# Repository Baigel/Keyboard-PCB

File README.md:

# Keyboard-PCB
A collection of PCB keyboards that run QMK - all in various states of completion

### Changes to Make
To PCBs
 - Oscillator to C122519
- Oscillator Load Caps to 20pF (including lcsc)
- Fix LEDs LCSC code to be correct (make sure it is C5149201)
- CC pins on USB C should be 5.1k
- Add lcsc C5156480 to sockets
- USB C to C2927038
- Change all diodes to C5345962
- Make sure Ctrl then Win then Alt
- Change Fn to Win

To Firmware:
 - Add separate firmware for different boards where relevatn
 - Add MacOS firmware versions

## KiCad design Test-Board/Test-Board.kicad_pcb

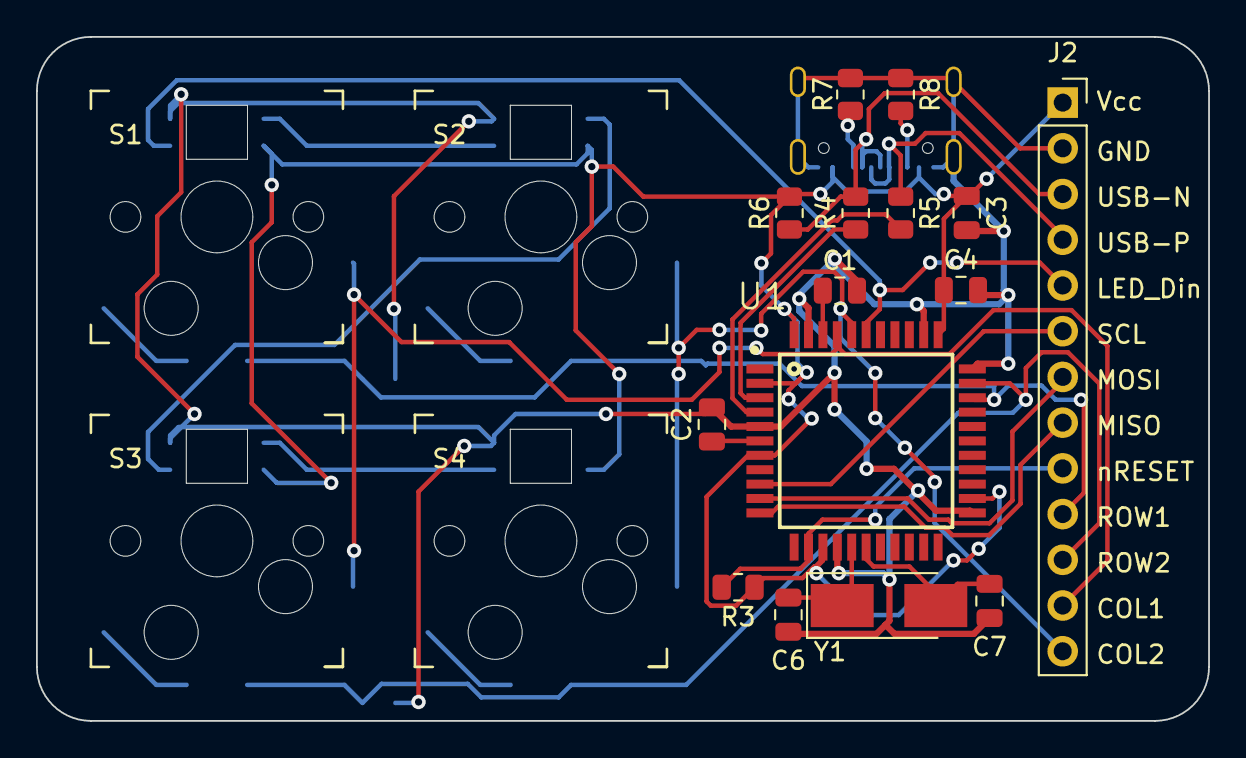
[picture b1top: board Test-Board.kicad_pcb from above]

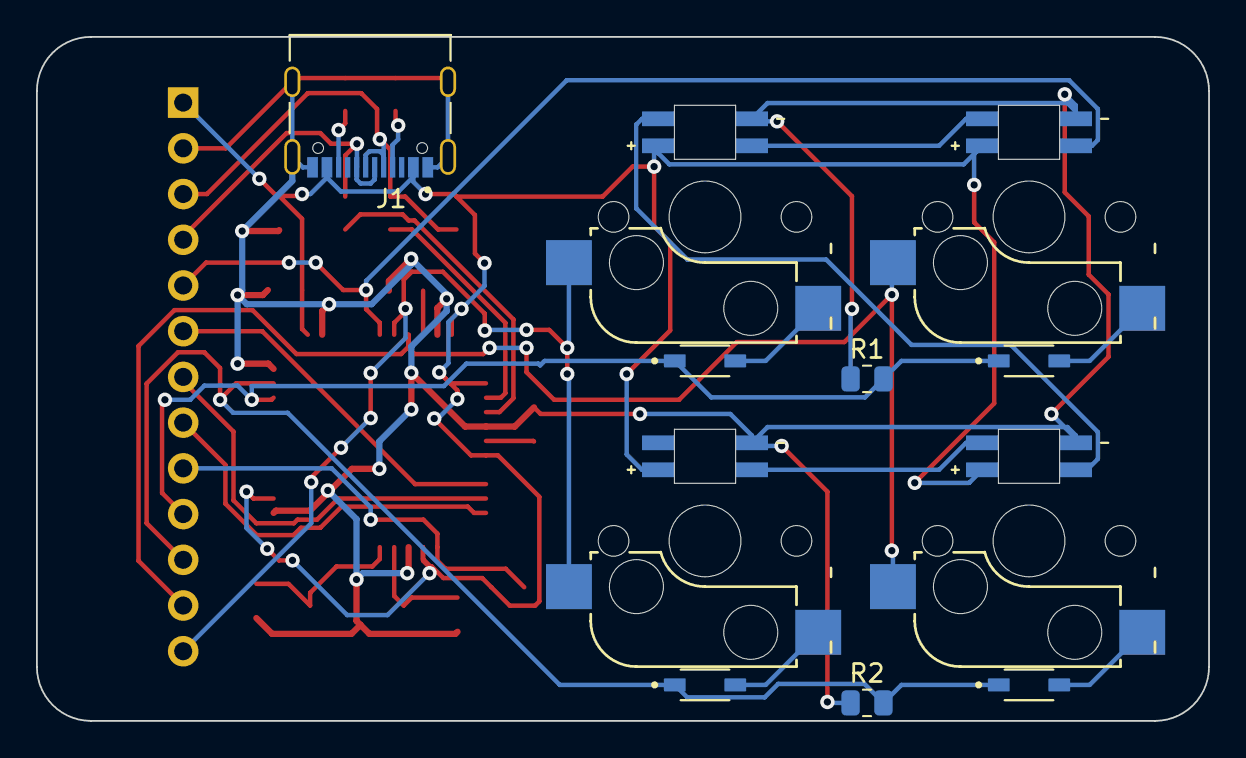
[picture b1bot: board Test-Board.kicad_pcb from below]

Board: 2 copper layers, 65.1 x 38.0 mm, 30 parts (11 on the bottom side), 28 nets.

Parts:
C1, C3: 0.1uF; C_0805_2012Metric
C2, C4: 1uF; C_0805_2012Metric
C6, C7: 20pF; C_0805_2012Metric
D1, D2, D3, D4: 1N4148; SOD3715X135N
J1: TYPE-C-31-M-12; HRO_TYPE-C-31-M-12
J2: Conn_01x13_Pin; PinSocket_1x13_P2.54mm_Vertical
L1, L2, L3, L4: SK6812-E; LED_SK6812-E
R1, R2, R3, R7, R8: 10k; R_0805_2012Metric
R4, R5: 22R; R_0805_2012Metric
R6: 15k; R_0805_2012Metric
SW1: S1; Kailh_socket_MX
SW2: S2; Kailh_socket_MX
SW3: S3; Kailh_socket_MX
SW4: S4; Kailh_socket_MX
U1: ATMEGA32U4-AU; QFP80P1200X1200X120-44N
Y1: 16MHz; Crystal_SMD_5032-2Pin_5.0x3.2mm_HandSoldering

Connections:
AREF: C1.1, U1.42 (AREF)
COL1: J2.12, SW1.2, SW3.2, U1.41 (PF0)
COL2: J2.13, SW2.2, SW4.2, U1.40 (PF1)
GND: C1.2, C2.2, C3.2, C4.2, C6.1, C7.2, J1.A1_B12 (GND), J1.B1_A12 (GND), J1.S1 (SHIELD), J1.S2 (SHIELD), J1.S3 (SHIELD), J1.S4 (SHIELD), J2.2, L1.3 (GND), L2.3 (GND), L3.3 (GND), L4.3 (GND), R1.1, R2.1, R7.1, R8.1, U1.5 (UGND), U1.15 (GND), U1.23 (GND), U1.33 (PE2), U1.35 (GND), U1.43 (GND)
LED_DIN: J2.5, L1.4 (DIN), U1.39 (PF4)
MISO: J2.8, U1.11 (PB3)
MOSI: J2.7, U1.10 (PB2)
unnamed: D1.A, SW1.1
unnamed: D2.A, SW2.1
unnamed: D3.A, SW3.1
unnamed: D4.A, SW4.1
unnamed: J1.A5 (CC1), R7.2
unnamed: J1.B5 (CC2), R8.2
unnamed: L1.2 (DOUT), L2.4 (DIN)
unnamed: L2.2 (DOUT), L3.4 (DIN)
unnamed: L3.2 (DOUT), L4.4 (DIN)
unnamed: R5.1, U1.4 (D+)
unnamed: R4.1, U1.3 (D-)
ROW1: D1.C, D2.C, J2.10, R1.2, U1.31 (PC6)
ROW2: D3.C, D4.C, J2.11, R2.2, U1.32 (PC7)
SCL: J2.6, U1.9 (PB1)
UCAP: C2.1, U1.6 (UCAP)
USB-N: J1.A7 (DN1), J1.B7 (DN2), J2.3, R4.2, R6.1
USB-P: J1.A6 (DP1), J1.B6 (DP2), J2.4, R5.2
VCC: C3.1, C4.1, J1.A4_B9 (VBUS), J1.B4_A9 (VBUS), J2.1, L1.1 (VDD), L2.1 (VDD), L3.1 (VDD), L4.1 (VDD), R3.1, R6.2, U1.2 (UVCC), U1.7 (VBUS), U1.14 (VCC), U1.24 (AVCC), U1.34 (VCC), U1.44 (AVCC)
XTAL1: C7.1, U1.17 (XTAL1), Y1.2
XTAL2: C6.2, U1.16 (XTAL2), Y1.1
nRESET: J2.9, R3.2, U1.13 (~RESET)

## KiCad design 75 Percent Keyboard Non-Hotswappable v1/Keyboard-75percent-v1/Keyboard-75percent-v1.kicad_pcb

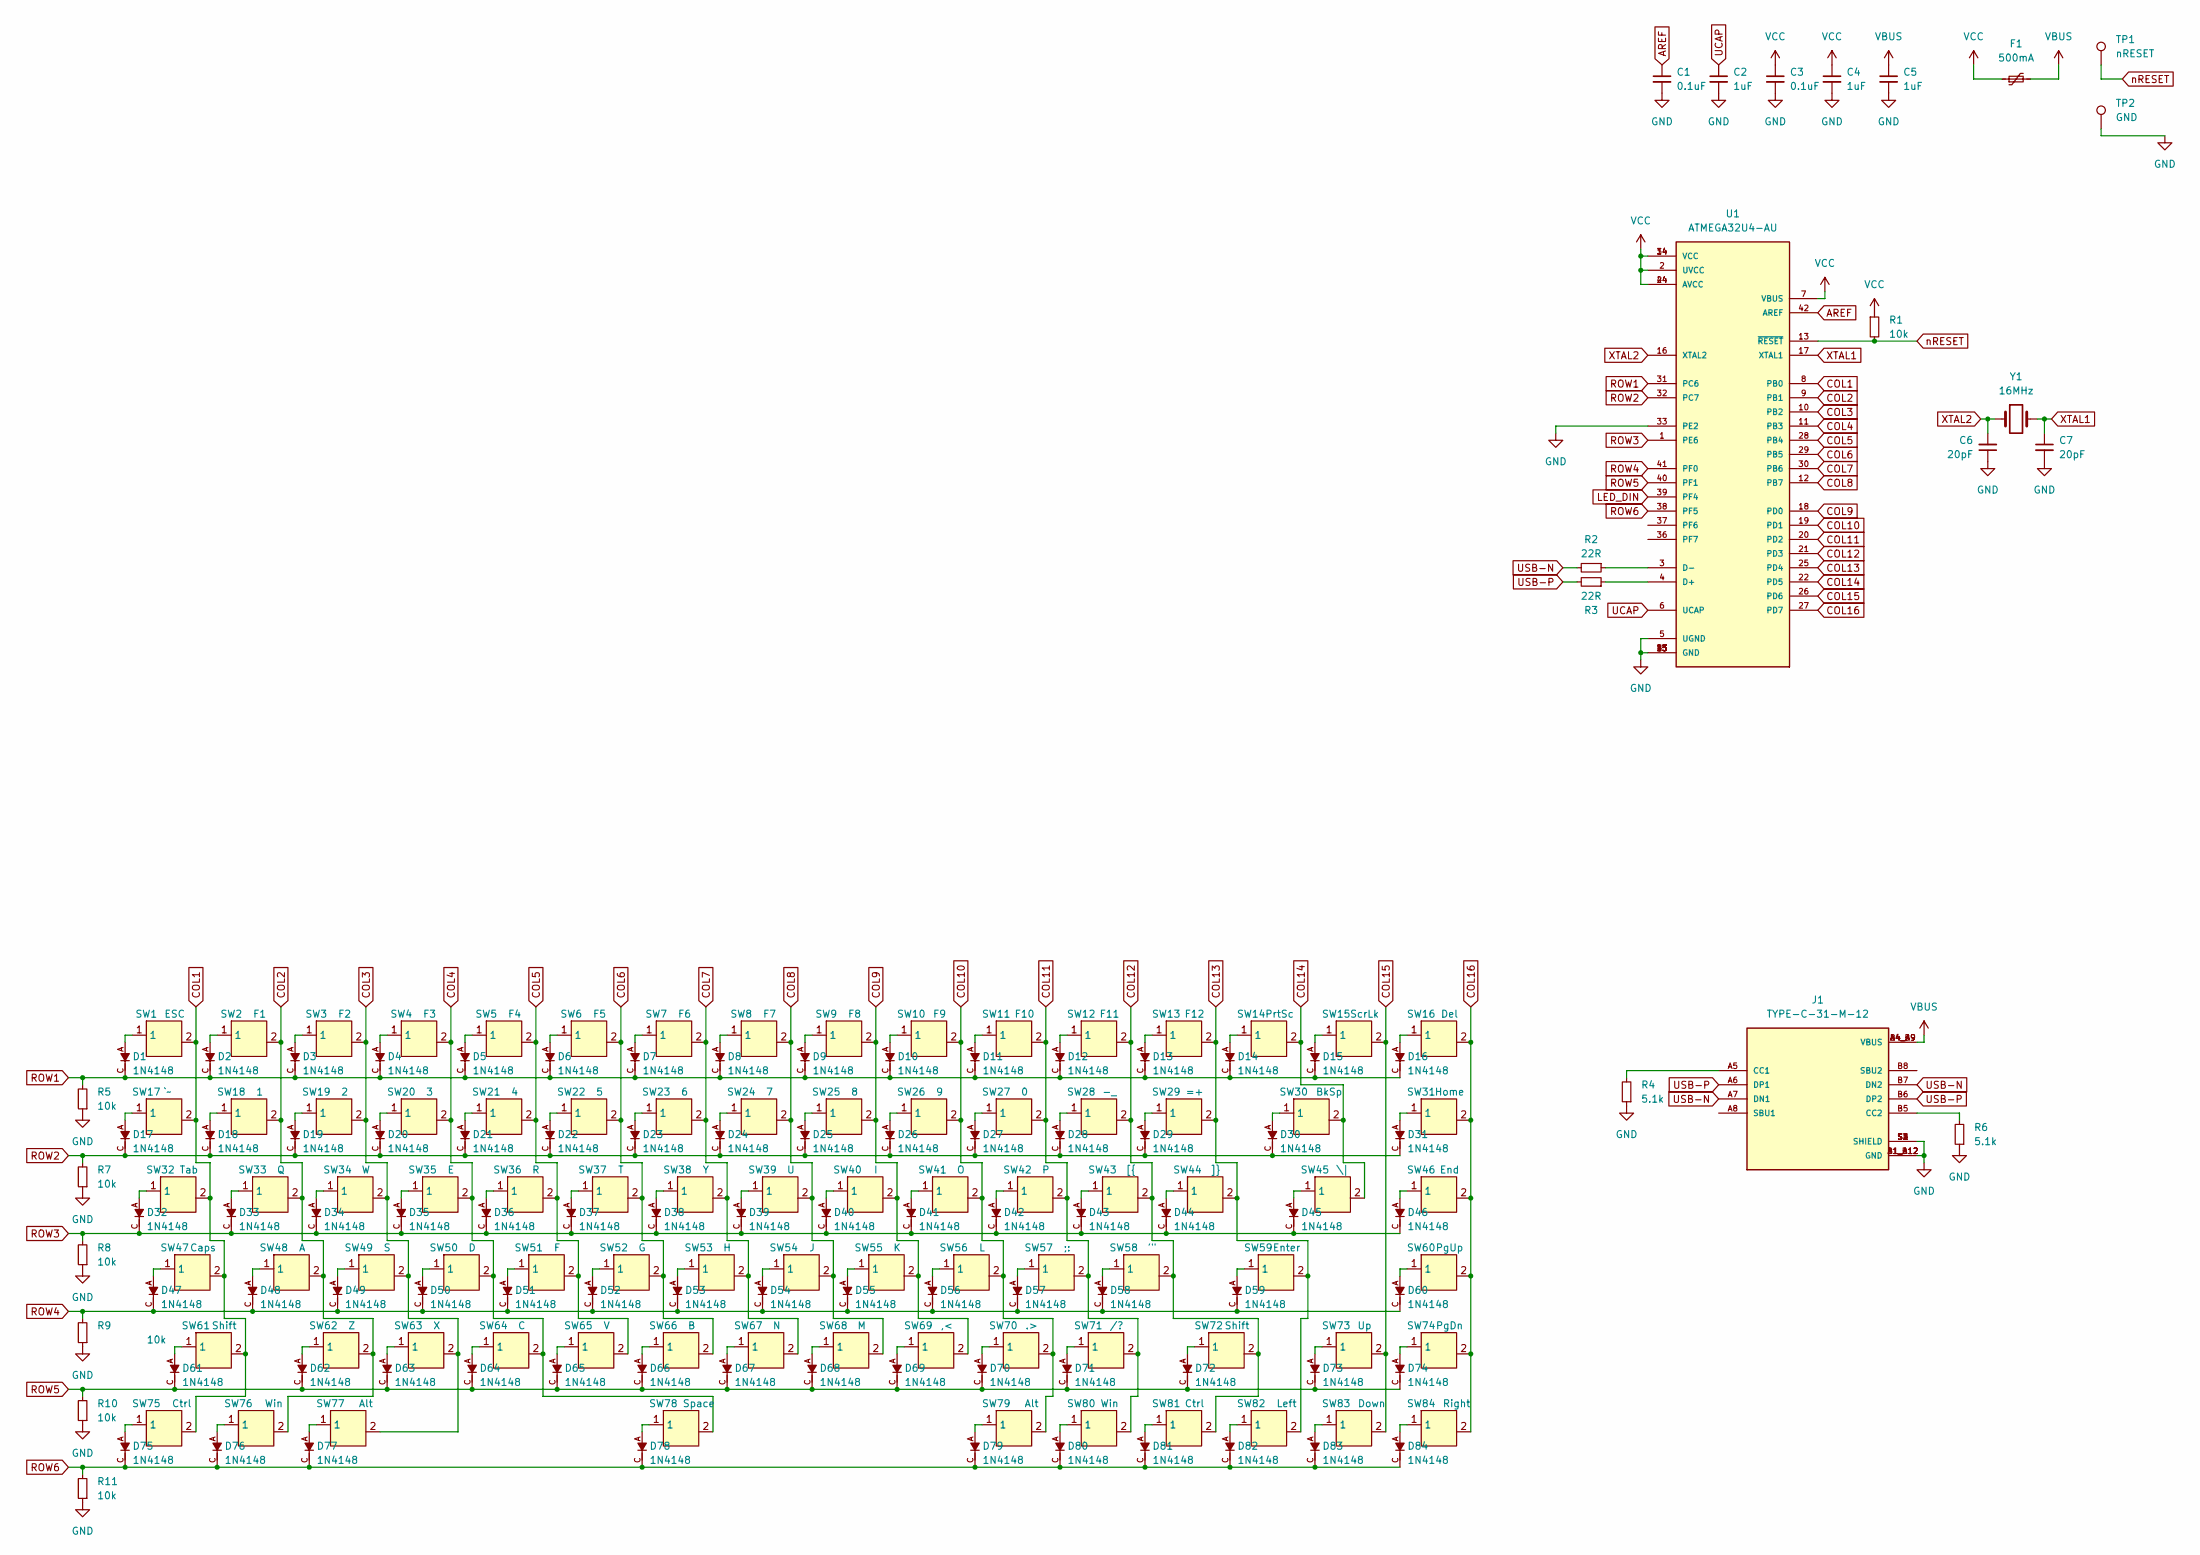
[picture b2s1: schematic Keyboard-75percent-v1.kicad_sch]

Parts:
C1, C3: 0.1uF; C_0805_2012Metric; LCSC C476766
C2, C4, C5: 1uF; C_0805_2012Metric; LCSC C152857
C6, C7: 20pF; C_0805_2012Metric; LCSC C2209222
D1, D2, D3, D4, D5, D6, D7, D8, D9, D10, D11, D12, D13, D14, D15, D16, D17, D18, D19, D20, D21, D22, D23, D24, D25, D26, D27, D28, D29, D30, D31, D32, D33, D34, D35, D36, D37, D38, D39, D40, D41, D42, D43, D44, D45, D46, D47, D48, D49, D50, D51, D52, D53, D54, D55, D56, D57, D58, D59, D60, D61, D62, D63, D64, D65, D66, D67, D68, D69, D70, D71, D72, D73, D74, D75, D76, D77, D78, D79, D80, D81, D82, D83, D84: 1N4148; SOD3715X135N; PARTREV 28-2; LCSC C5345962
F1: 500mA; R_0805_2012Metric_Pad1.20x1.40mm_HandSolder; LCSC C2649565
J1: TYPE-C-31-M-12; HRO_TYPE-C-31-M-12; PARTREV 2020.12.08; LCSC C2927038
R1, R5, R7, R8, R9, R10, R11: 10k; R_0805_2012Metric; LCSC C2075621
R2, R3: 22R; R_0805_2012Metric; LCSC C4349165
R4, R6: 5.1k; R_0805_2012Metric; LCSC C2079038
SW1: ESC; SW_Cherry_MX_1.00u_PCB
SW2: F1; SW_Cherry_MX_1.00u_PCB
SW3: F2; SW_Cherry_MX_1.00u_PCB
SW4: F3; SW_Cherry_MX_1.00u_PCB
SW5: F4; SW_Cherry_MX_1.00u_PCB
SW6: F5; SW_Cherry_MX_1.00u_PCB
SW7: F6; SW_Cherry_MX_1.00u_PCB
SW8: F7; SW_Cherry_MX_1.00u_PCB
SW9: F8; SW_Cherry_MX_1.00u_PCB
SW10: F9; SW_Cherry_MX_1.00u_PCB
SW11: F10; SW_Cherry_MX_1.00u_PCB
SW12: F11; SW_Cherry_MX_1.00u_PCB
SW13: F12; SW_Cherry_MX_1.00u_PCB
SW14: PrtSc; SW_Cherry_MX_1.00u_PCB
SW15: ScrLk; SW_Cherry_MX_1.00u_PCB
SW16: Del; SW_Cherry_MX_1.00u_PCB
SW17: `~; SW_Cherry_MX_1.00u_PCB
SW18: 1; SW_Cherry_MX_1.00u_PCB
SW19: 2; SW_Cherry_MX_1.00u_PCB
SW20: 3; SW_Cherry_MX_1.00u_PCB
SW21: 4; SW_Cherry_MX_1.00u_PCB
SW22: 5; SW_Cherry_MX_1.00u_PCB
SW23: 6; SW_Cherry_MX_1.00u_PCB
SW24: 7; SW_Cherry_MX_1.00u_PCB
SW25: 8; SW_Cherry_MX_1.00u_PCB
SW26: 9; SW_Cherry_MX_1.00u_PCB
SW27: 0; SW_Cherry_MX_1.00u_PCB
SW28: -_; SW_Cherry_MX_1.00u_PCB
SW29: =+; SW_Cherry_MX_1.00u_PCB
SW30: BkSp; SW_Cherry_MX_2.00u_PCB
SW31: Home; SW_Cherry_MX_1.00u_PCB
SW32: Tab; SW_Cherry_MX_1.50u_PCB
SW33: Q; SW_Cherry_MX_1.00u_PCB
SW34: W; SW_Cherry_MX_1.00u_PCB
SW35: E; SW_Cherry_MX_1.00u_PCB
SW36: R; SW_Cherry_MX_1.00u_PCB
SW37: T; SW_Cherry_MX_1.00u_PCB
SW38: Y; SW_Cherry_MX_1.00u_PCB
SW39: U; SW_Cherry_MX_1.00u_PCB
SW40: I; SW_Cherry_MX_1.00u_PCB
SW41: O; SW_Cherry_MX_1.00u_PCB
SW42: P; SW_Cherry_MX_1.00u_PCB
SW43: [{; SW_Cherry_MX_1.00u_PCB
SW44: ]}; SW_Cherry_MX_1.00u_PCB
SW45: \|; SW_Cherry_MX_1.50u_PCB
SW46: End; SW_Cherry_MX_1.00u_PCB
SW47: Caps; SW_Cherry_MX_1.75u_PCB
SW48: A; SW_Cherry_MX_1.00u_PCB
SW49: S; SW_Cherry_MX_1.00u_PCB
SW50: D; SW_Cherry_MX_1.00u_PCB
SW51: F; SW_Cherry_MX_1.00u_PCB
SW52: G; SW_Cherry_MX_1.00u_PCB
SW53: H; SW_Cherry_MX_1.00u_PCB
SW54: J; SW_Cherry_MX_1.00u_PCB
SW55: K; SW_Cherry_MX_1.00u_PCB
SW56: L; SW_Cherry_MX_1.00u_PCB
SW57: ;:; SW_Cherry_MX_1.00u_PCB
SW58: '"; SW_Cherry_MX_1.00u_PCB
SW59: Enter; SW_Cherry_MX_2.25u_PCB
SW60: PgUp; SW_Cherry_MX_1.00u_PCB
SW61: Shift; SW_Cherry_MX_2.25u_PCB
SW62: Z; SW_Cherry_MX_1.00u_PCB
SW63: X; SW_Cherry_MX_1.00u_PCB
SW64: C; SW_Cherry_MX_1.00u_PCB
SW65: V; SW_Cherry_MX_1.00u_PCB
SW66: B; SW_Cherry_MX_1.00u_PCB
SW67: N; SW_Cherry_MX_1.00u_PCB
SW68: M; SW_Cherry_MX_1.00u_PCB
SW69: ,<; SW_Cherry_MX_1.00u_PCB
SW70: .>; SW_Cherry_MX_1.00u_PCB
SW71: /?; SW_Cherry_MX_1.00u_PCB
SW72: Shift; SW_Cherry_MX_1.75u_PCB
SW73: Up; SW_Cherry_MX_1.00u_PCB
SW74: PgDn; SW_Cherry_MX_1.00u_PCB
SW75: Ctrl; SW_Cherry_MX_1.25u_PCB
SW76: Win; SW_Cherry_MX_1.25u_PCB
SW77: Alt; SW_Cherry_MX_1.25u_PCB
SW78: Space; SW_Cherry_MX_6.25u_PCB
SW79: Alt; SW_Cherry_MX_1.00u_PCB
SW80: Win; SW_Cherry_MX_1.00u_PCB
SW81: Ctrl; SW_Cherry_MX_1.00u_PCB
SW82: Left; SW_Cherry_MX_1.00u_PCB
SW83: Down; SW_Cherry_MX_1.00u_PCB
SW84: Right; SW_Cherry_MX_1.00u_PCB
TP1: nRESET; TestPoint_Pad_D2.0mm
TP2: GND; TestPoint_Pad_D2.0mm
U1: ATMEGA32U4-AU; QFP80P1200X1200X120-44N
Y1: 16MHz; Crystal_SMD_5032-2Pin_5.0x3.2mm_HandSoldering; LCSC C122519

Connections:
AREF: C1.1, U1.42 (AREF)
COL1: SW1.2, SW17.2, SW32.2, SW47.2, SW61.2, SW75.2, U1.8 (PB0)
COL2: SW2.2, SW18.2, SW33.2, SW48.2, SW62.2, SW76.2, U1.9 (PB1)
COL3: SW3.2, SW19.2, SW34.2, SW49.2, SW63.2, SW77.2, U1.10 (PB2)
COL4: SW4.2, SW20.2, SW35.2, SW50.2, SW64.2, SW78.2, U1.11 (PB3)
COL5: SW5.2, SW21.2, SW36.2, SW51.2, SW65.2, U1.28 (PB4)
COL6: SW6.2, SW22.2, SW37.2, SW52.2, SW66.2, U1.29 (PB5)
COL7: SW7.2, SW23.2, SW38.2, SW53.2, SW67.2, U1.30 (PB6)
COL8: SW8.2, SW24.2, SW39.2, SW54.2, SW68.2, U1.12 (PB7)
COL9: SW9.2, SW25.2, SW40.2, SW55.2, SW69.2, U1.18 (PD0)
COL10: SW10.2, SW26.2, SW41.2, SW56.2, SW70.2, SW79.2, U1.19 (PD1)
COL11: SW11.2, SW27.2, SW42.2, SW57.2, SW71.2, SW80.2, U1.20 (PD2)
COL12: SW12.2, SW28.2, SW43.2, SW58.2, SW72.2, SW81.2, U1.21 (PD3)
COL13: SW13.2, SW29.2, SW44.2, SW59.2, SW82.2, U1.25 (PD4)
COL14: SW14.2, SW30.2, SW45.2, U1.22 (PD5)
COL15: SW15.2, SW73.2, SW83.2, U1.26 (PD6)
COL16: SW16.2, SW31.2, SW46.2, SW60.2, SW74.2, SW84.2, U1.27 (PD7)
GND: C1.2, C2.2, C3.2, C4.2, C5.2, C6.1, C7.2, J1.A1_B12 (GND), J1.B1_A12 (GND), J1.S1 (SHIELD), J1.S2 (SHIELD), J1.S3 (SHIELD), J1.S4 (SHIELD), R4.1, R5.1, R6.1, R7.1, R8.1, R9.1, R10.1, R11.1, TP2.1, U1.5 (UGND), U1.15 (GND), U1.23 (GND), U1.33 (PE2), U1.35 (GND), U1.43 (GND)
LED_DIN: U1.39 (PF4)
unnamed: D1.A, SW1.1
unnamed: D2.A, SW2.1
unnamed: D3.A, SW3.1
unnamed: D4.A, SW4.1
unnamed: D5.A, SW5.1
unnamed: D6.A, SW6.1
unnamed: D7.A, SW7.1
unnamed: D8.A, SW8.1
unnamed: D9.A, SW9.1
unnamed: D10.A, SW10.1
unnamed: D11.A, SW11.1
unnamed: D12.A, SW12.1
unnamed: D13.A, SW13.1
unnamed: D14.A, SW14.1
unnamed: D15.A, SW15.1
unnamed: D16.A, SW16.1
unnamed: D17.A, SW17.1
unnamed: D18.A, SW18.1
unnamed: D19.A, SW19.1
unnamed: D20.A, SW20.1
unnamed: D21.A, SW21.1
unnamed: D22.A, SW22.1
unnamed: D23.A, SW23.1
unnamed: D24.A, SW24.1
unnamed: D25.A, SW25.1
unnamed: D26.A, SW26.1
unnamed: D27.A, SW27.1
unnamed: D28.A, SW28.1
unnamed: D29.A, SW29.1
unnamed: D30.A, SW30.1
unnamed: D31.A, SW31.1
unnamed: D32.A, SW32.1
unnamed: D33.A, SW33.1
unnamed: D34.A, SW34.1
unnamed: D35.A, SW35.1
unnamed: D36.A, SW36.1
unnamed: D37.A, SW37.1
unnamed: D38.A, SW38.1
unnamed: D39.A, SW39.1
unnamed: D40.A, SW40.1
unnamed: D41.A, SW41.1
unnamed: D42.A, SW42.1
unnamed: D43.A, SW43.1
unnamed: D44.A, SW44.1
unnamed: D45.A, SW45.1
unnamed: D46.A, SW46.1
unnamed: D47.A, SW47.1
unnamed: D48.A, SW48.1
unnamed: D49.A, SW49.1
unnamed: D50.A, SW50.1
unnamed: D51.A, SW51.1
unnamed: D52.A, SW52.1
unnamed: D53.A, SW53.1
unnamed: D54.A, SW54.1
unnamed: D55.A, SW55.1
unnamed: D56.A, SW56.1
unnamed: D57.A, SW57.1
unnamed: D58.A, SW58.1
unnamed: D59.A, SW59.1
unnamed: D60.A, SW60.1
unnamed: D61.A, SW61.1
unnamed: D62.A, SW62.1
unnamed: D63.A, SW63.1
unnamed: D64.A, SW64.1
unnamed: D65.A, SW65.1
unnamed: D66.A, SW66.1
unnamed: D67.A, SW67.1
unnamed: D68.A, SW68.1
unnamed: D69.A, SW69.1
unnamed: D70.A, SW70.1
unnamed: D71.A, SW71.1
unnamed: D72.A, SW72.1
unnamed: D73.A, SW73.1
unnamed: D74.A, SW74.1
unnamed: D75.A, SW75.1
unnamed: D76.A, SW76.1
unnamed: D77.A, SW77.1
unnamed: D78.A, SW78.1
unnamed: D79.A, SW79.1
unnamed: D80.A, SW80.1
unnamed: D81.A, SW81.1
unnamed: D82.A, SW82.1
unnamed: D83.A, SW83.1
unnamed: D84.A, SW84.1
unnamed: J1.A5 (CC1), R4.2
unnamed: J1.B5 (CC2), R6.2
unnamed: R3.1, U1.4 (D+)
unnamed: R2.1, U1.3 (D-)
ROW1: D1.C, D2.C, D3.C, D4.C, D5.C, D6.C, D7.C, D8.C, D9.C, D10.C, D11.C, D12.C, D13.C, D14.C, D15.C, D16.C, R5.2, U1.31 (PC6)
ROW2: D17.C, D18.C, D19.C, D20.C, D21.C, D22.C, D23.C, D24.C, D25.C, D26.C, D27.C, D28.C, D29.C, D30.C, D31.C, R7.2, U1.32 (PC7)
ROW3: D32.C, D33.C, D34.C, D35.C, D36.C, D37.C, D38.C, D39.C, D40.C, D41.C, D42.C, D43.C, D44.C, D45.C, D46.C, R8.2, U1.1 (PE6)
ROW4: D47.C, D48.C, D49.C, D50.C, D51.C, D52.C, D53.C, D54.C, D55.C, D56.C, D57.C, D58.C, D59.C, D60.C, R9.2, U1.41 (PF0)
ROW5: D61.C, D62.C, D63.C, D64.C, D65.C, D66.C, D67.C, D68.C, D69.C, D70.C, D71.C, D72.C, D73.C, D74.C, R10.2, U1.40 (PF1)
ROW6: D75.C, D76.C, D77.C, D78.C, D79.C, D80.C, D81.C, D82.C, D83.C, D84.C, R11.2, U1.38 (PF5)
UCAP: C2.1, U1.6 (UCAP)
USB-N: J1.A7 (DN1), J1.B7 (DN2), R2.2
USB-P: J1.A6 (DP1), J1.B6 (DP2), R3.2
VBUS: C5.1, F1.2, J1.A4_B9 (VBUS), J1.B4_A9 (VBUS)
VCC: C3.1, C4.1, F1.1, R1.1, U1.2 (UVCC), U1.7 (VBUS), U1.14 (VCC), U1.24 (AVCC), U1.34 (VCC), U1.44 (AVCC)
XTAL1: C7.1, U1.17 (XTAL1), Y1.2
XTAL2: C6.2, U1.16 (XTAL2), Y1.1
nRESET: R1.2, TP1.1, U1.13 (~RESET)

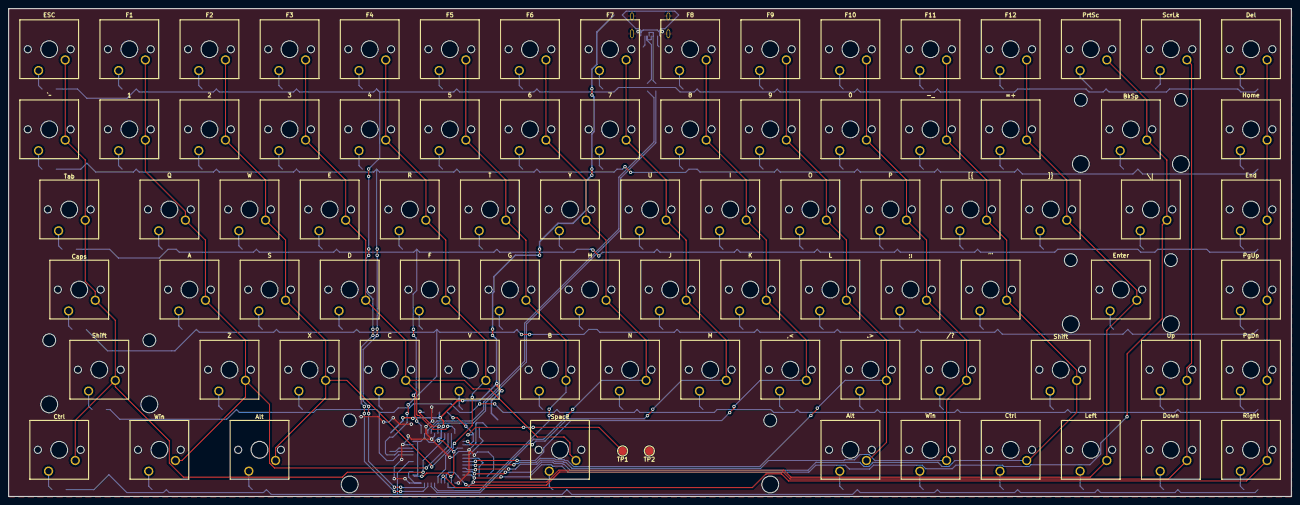
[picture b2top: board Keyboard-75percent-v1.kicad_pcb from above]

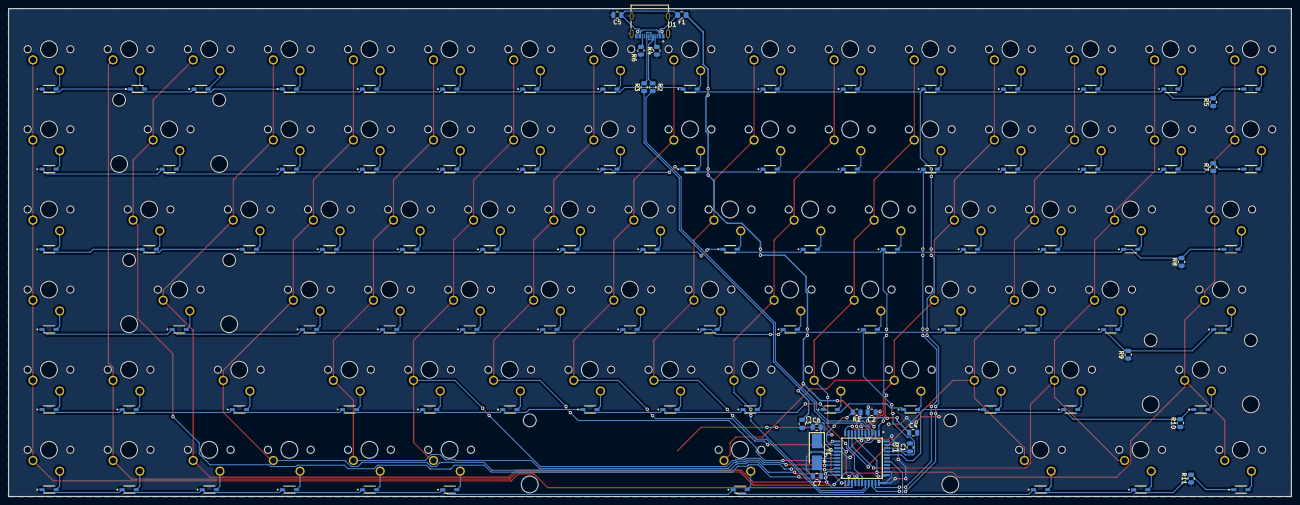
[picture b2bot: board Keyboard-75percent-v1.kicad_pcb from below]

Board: 2 copper layers, 305.0 x 116.0 mm, 192 parts (106 on the bottom side), 120 nets.

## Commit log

2026-03-03 initial commit with KiCad PCB files
2026-03-03 fixed .gitignore
2026-03-04 added firmware
2026-03-05 Added test board PCB
2026-03-06 added details in Readme regarding things still to do
